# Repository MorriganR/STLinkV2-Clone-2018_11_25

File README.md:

# STLinkV2-Clone-2018_11_25
STLinkV2 Clone 2018_11_25

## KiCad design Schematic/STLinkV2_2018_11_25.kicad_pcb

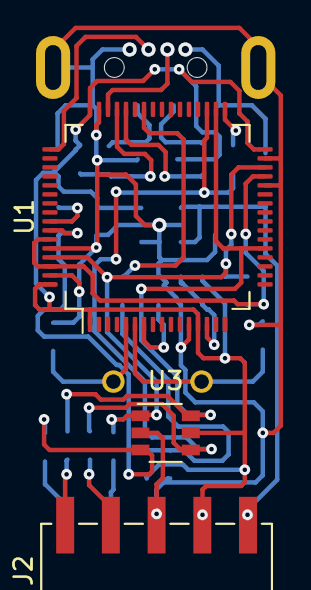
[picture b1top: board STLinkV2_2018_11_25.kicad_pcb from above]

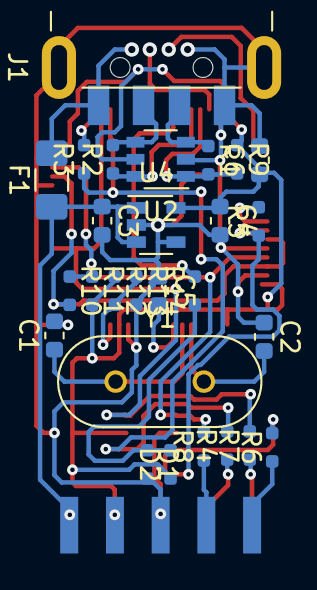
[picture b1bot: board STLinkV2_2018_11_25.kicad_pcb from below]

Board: 2 copper layers, 30 parts (27 on the bottom side), 25 nets.

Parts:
C1, C2: 20p; C_0603_1608Metric
C3, C4, C5, C6: 0.1; C_0603_1608Metric
D1: B; R_0402_1005Metric
D2: R; R_0402_1005Metric
F1: Polyfuse_Small; Fuse_1206_3216Metric_Pad1.42x1.75mm_HandSolder
J1: USB_A; USB_A_CNCTech_1001-011-01101_Horizontal
J2: Conn_02x05_Odd_Even; PinHeader_2x05_P2.54mm_Vertical_SMD
R1, R2: 22; R_0402_1005Metric
R3, R4, R6, R7, R8: 100; R_0402_1005Metric
R5, R10: 220; R_0402_1005Metric
R9, R14: 1.8k; R_0402_1005Metric
R11: 680; R_0402_1005Metric
R12, R13: 10k; R_0402_1005Metric
U1: STM32F103RBTx; LQFP-64_10x10mm_P0.5mm
U2, U3: SRV05-4; SOT-23-6
U4: TLV71333PDBV; SOT-23-5
Y1: 8.0MHz; Crystal_HC18-U_Vertical

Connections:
+3V3: C4.1, C6.1, D2.1, J2.7, J2.8, R9.1, R11.2, R12.1, U1.1, U1.13, U1.32, U1.48, U1.64, U2.5, U3.5, U4.5
/+5V: C3.1, F1.1, J2.9, J2.10, U4.1, U4.3
/+5VU: F1.2, J1.1
/D+: J1.3, R1.1, U2.3
/D-: J1.2, R2.2, U2.4
/LED_STLINK: D1.1, D2.2, R14.1
/NRST: C5.2, U1.7
/OSCIN: C2.2, U1.5, Y1.2
/OSCOUT: C1.1, U1.6, Y1.1
/PA0: R12.2, R13.1, U1.14
/PA9: R14.2, U1.42
/PB5: R5.2, U1.57
/PB7: R10.2, U1.29, U1.59, U1.62
/PB12: R3.2, U1.33
/RST: R5.1, R6.2, U1.58, U3.3
/RST_R: J2.1, R6.1
/SWCLK: R7.2, U1.21, U1.34, U3.6
/SWCLK_R: J2.2, R7.1
/SWDIO: R3.1, R4.2, U1.35, U3.4
/SWDIO_R: J2.4, R4.1
/SWIM: R8.2, R10.1, R11.1, U1.30, U1.61, U3.1
/SWIM_R: J2.3, R8.1
/USB+: R1.2, R9.2, U1.45, U2.1
/USB-: R2.1, U1.44, U2.6
GNDD: C1.2, C2.1, C3.2, C4.2, C5.1, C6.2, D1.2, J1.4, J1.5, J2.5, J2.6, R13.2, U1.12, U1.28, U1.31, U1.47, U1.60, U1.63, U2.2, U3.2, U4.2, U4.4
